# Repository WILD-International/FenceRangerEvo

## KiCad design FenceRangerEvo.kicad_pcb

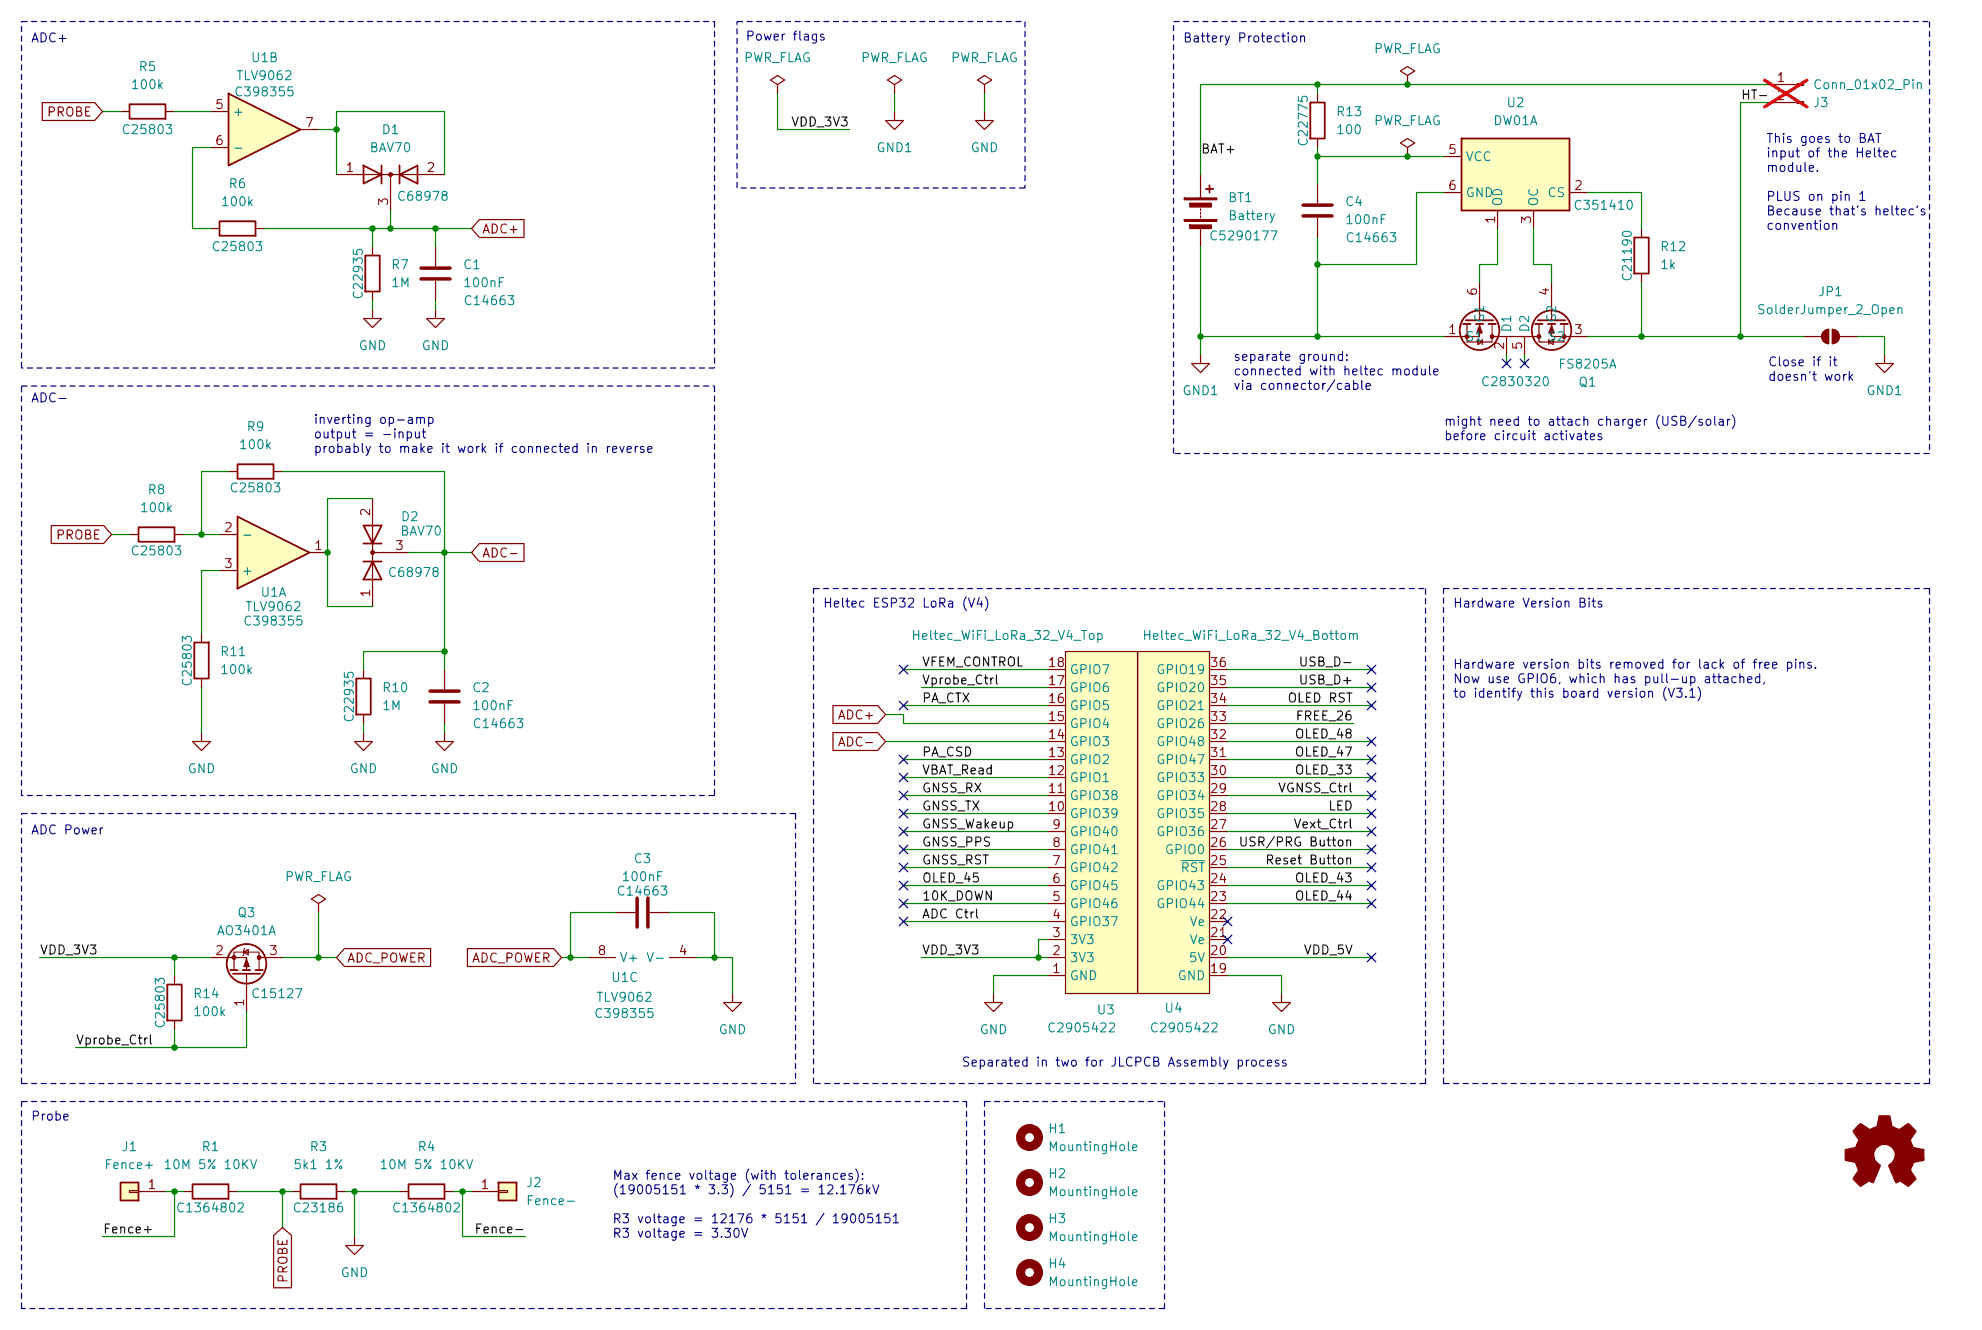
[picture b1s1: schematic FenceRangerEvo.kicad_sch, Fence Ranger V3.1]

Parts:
BT1: Battery; BH-123A-A1CJ002; LCSC C5290177
C1, C2, C3, C4: 100nF; C_0603_1608Metric; LCSC C14663
D1, D2: BAV70; SOT-23; LCSC C68978
H1, H2, H3, H4: MountingHole; MountingHole_3.2mm_M3_ISO7380_Pad
J1: Fence+; SolderWire-1sqmm_1x01_D1.4mm_OD3.9mm
J2: Fence-; SolderWire-1sqmm_1x01_D1.4mm_OD3.9mm
J3: Conn_01x02_Pin; PinHeader_2x01_P2.54mm_Vertical; not fitted
JP1: SolderJumper_2_Open; SolderJumper-2_P1.3mm_Open_RoundedPad1.0x1.5mm
Q1: FS8205A; SOT-23-6; LCSC C2830320
Q3: AO3401A; SOT-23; LCSC C15127
R1, R4: 10M 5% 10KV; R_Axial_DIN0918_L18.0mm_D9.0mm_P22.86mm_Horizontal; LCSC C1364802
R3: 5k1 1%; R_0603_1608Metric; LCSC C23186
R5, R6, R8, R9, R11, R14: 100k; R_0603_1608Metric; LCSC C25803
R7, R10: 1M; R_0603_1608Metric; LCSC C22935
R12: 1k; R_0603_1608Metric; LCSC C21190
R13: 100; R_0603_1608Metric; LCSC C22775
U1: TLV9062; SOIC-8_3.9x4.9mm_P1.27mm; LCSC C398355
U2: DW01A; SOT-23-6; LCSC C351410
U3: Heltec_WiFi_LoRa_32_V4_Top; Heltec ESP32 V4 module top; LCSC C2905422
U4: Heltec_WiFi_LoRa_32_V4_Bottom; Heltec ESP32 V4 module bottom; LCSC C2905422

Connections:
/10K_DOWN: U3.5 (GPIO46)
/ADC Ctrl: U3.4 (GPIO37)
/BAT+: BT1.1 (+), J3.1, R13.1
/FREE_26: U4.33 (GPIO26)
/Fence+: J1.1 (Pin_1_1), R1.1
/Fence-: J2.1 (Pin_1_1), R4.2
/GNSS_PPS: U3.8 (GPIO41)
/GNSS_RST: U3.7 (GPIO42)
/GNSS_RX: U3.11 (GPIO38)
/GNSS_TX: U3.10 (GPIO39)
/GNSS_Wakeup: U3.9 (GPIO40)
/HT-: J3.2, JP1.1 (A), Q1.3 (S2), R12.2
/LED: U4.28 (GPIO35)
/OLED RST: U4.34 (GPIO21)
/OLED_33: U4.30 (GPIO33)
/OLED_43: U4.24 (GPIO43)
/OLED_44: U4.23 (GPIO44)
/OLED_45: U3.6 (GPIO45)
/OLED_47: U4.31 (GPIO47)
/OLED_48: U4.32 (GPIO48)
/PA_CSD: U3.13 (GPIO2)
/PA_CTX: U3.16 (GPIO5)
/Reset Button: U4.25 (~RST)
/USB_D+: U4.35 (GPIO20)
/USB_D-: U4.36 (GPIO19)
/USR/PRG Button: U4.26 (GPIO0)
/VBAT_Read: U3.12 (GPIO1)
/VDD_3V3: Q3.2 (S), R14.1, U3.2 (3V3), U3.3 (3V3)
/VDD_5V: U4.20 (5V)
/VFEM_CONTROL: U3.18 (GPIO7)
/VGNSS_Ctrl: U4.29 (GPIO34)
/Vext_Ctrl: U4.27 (GPIO36)
/Vprobe_Ctrl: Q3.1 (G), R14.2, U3.17 (GPIO6)
ADC+: C1.1, D1.3 (K), R6.2, R7.1, U3.15 (GPIO4)
ADC-: C2.1, D2.3 (K), R9.2, R10.1, U3.14 (GPIO3)
ADC_POWER: C3.1, Q3.3 (D), U1.8 (V+)
GND: C1.2, C2.2, C3.2, R3.2, R4.1, R7.2, R10.2, R11.1, U1.4 (V-), U3.1 (GND), U4.19 (GND)
GND1: BT1.2 (-), C4.2, JP1.2 (B), Q1.1 (S1), U2.6 (GND)
unnamed: D1.1 (A), D1.2 (A), U1.7
unnamed: D2.1 (A), D2.2 (A), U1.1
unnamed: Q1.6 (G1), U2.1 (OD)
unnamed: Q1.4 (G2), U2.3 (OC)
unnamed: R11.2, U1.3 (+)
unnamed: R8.2, R9.1, U1.2 (-)
unnamed: R5.2, U1.5 (+)
unnamed: R6.1, U1.6 (-)
unnamed: R12.1, U2.2 (CS)
unnamed: C4.1, R13.2, U2.5 (VCC)
PROBE: R1.2, R3.1, R5.1, R8.1

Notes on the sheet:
ADC+
Heltec ESP32 LoRa (V4)
might need to attach charger (USB/solar) before circuit activates
Max fence voltage (with tolerances): (19005151 * 3.3) / 5151 = 12.176kV R3 voltage = 12176 * 5151 / 19005151 R3 voltage = 3.30V
separate ground: connected with heltec module via connector/cable
Battery Protection
Hardware version bits removed for lack of free pins. Now use GPIO6, which has pull-up attached, to identify this board version (V3.1)
ADC-
Close if it doesn't work
Power flags
Probe
Hardware Version Bits
inverting op-amp output = -input probably to make it work if connected in reverse
This goes to BAT input of the Heltec module. PLUS on pin 1 Because that's heltec's convention
ADC Power
Separated in two for JLCPCB Assembly process

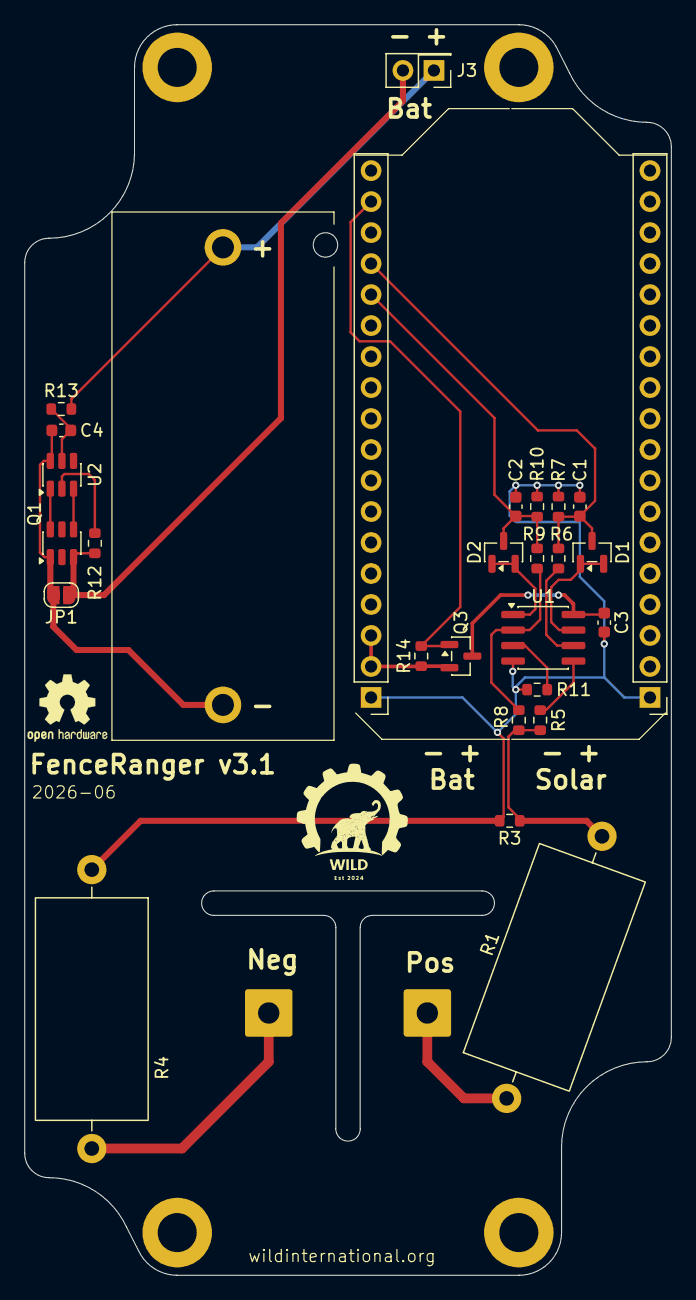
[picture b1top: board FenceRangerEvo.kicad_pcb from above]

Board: 2 copper layers, 53.0 x 102.5 mm, 34 parts (0 on the bottom side), 22 nets.

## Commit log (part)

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2025-12-20 Initial v3 version, WIP
2025-12-20 replace opamp vsop with soic-8 footprint
2025-12-20 replace AO3400 with 2N7002 signal mosfet
2025-12-22 fix battery placement, separate heltec module in 2 for placement
2025-12-22 minor changes for nicer groundplane routing
2025-12-22 add power resistors with jlc parts
2025-12-23 feedback willem written in schematic
2025-12-23 use DW01 with FS8205A for battery protection instead
2025-12-23 schematics: voltage divider 2x10M and 5.1k
2025-12-23 pcb layout with new protection circuit and voltage divider
2025-12-23 add LCSC part numbers for new components
2025-12-23 fix placement rotation of DW01A chip
2025-12-26 make schematics nicer with sections
2025-12-27 new FS8205A part number, improve comments on schematic
2025-12-30 add power flags, pass ERC
2025-12-30 generate production files for JLCPCB order
2026-06-03 add schematics pdf and datasheets
2026-06-03 .kicad_pro file update meta version 4->5
2026-06-03 .kicad_sch file update meta version 9->10
2026-06-03 fix measurment resistor LCSC part number: 5.1kOhm instead of wrong 5.1Ohm
2026-06-03 add datasheet for heltec v4.2 module
2026-06-03 move Vprobe_Ctrl to GPIO6 and mark all other occupied labels
2026-06-03 change Vprobe_Ctrl routing to GPIO6; remove version resistors
2026-06-03 bump version to 3.1 on pcb and schematic. remove version resistors silkscreen
2026-06-03 change pin headers part number
2026-06-03 production files for v3.1
